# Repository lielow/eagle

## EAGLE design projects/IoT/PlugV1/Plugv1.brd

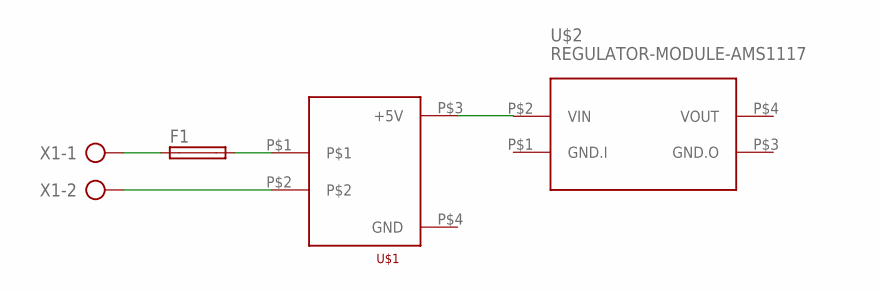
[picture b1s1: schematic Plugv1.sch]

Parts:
F1: SH22,5A
U$1: HLK-PM01
U$2: REGULATOR-MODULE-AMS1117
X1: AK500/2-H

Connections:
unnamed: F1.2, U$1.P$1
unnamed: F1.1, X1.1
unnamed: U$1.P$2, X1.2

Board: 2 copper layers, 4 parts (0 on the bottom side), 3 nets, no tracks yet.

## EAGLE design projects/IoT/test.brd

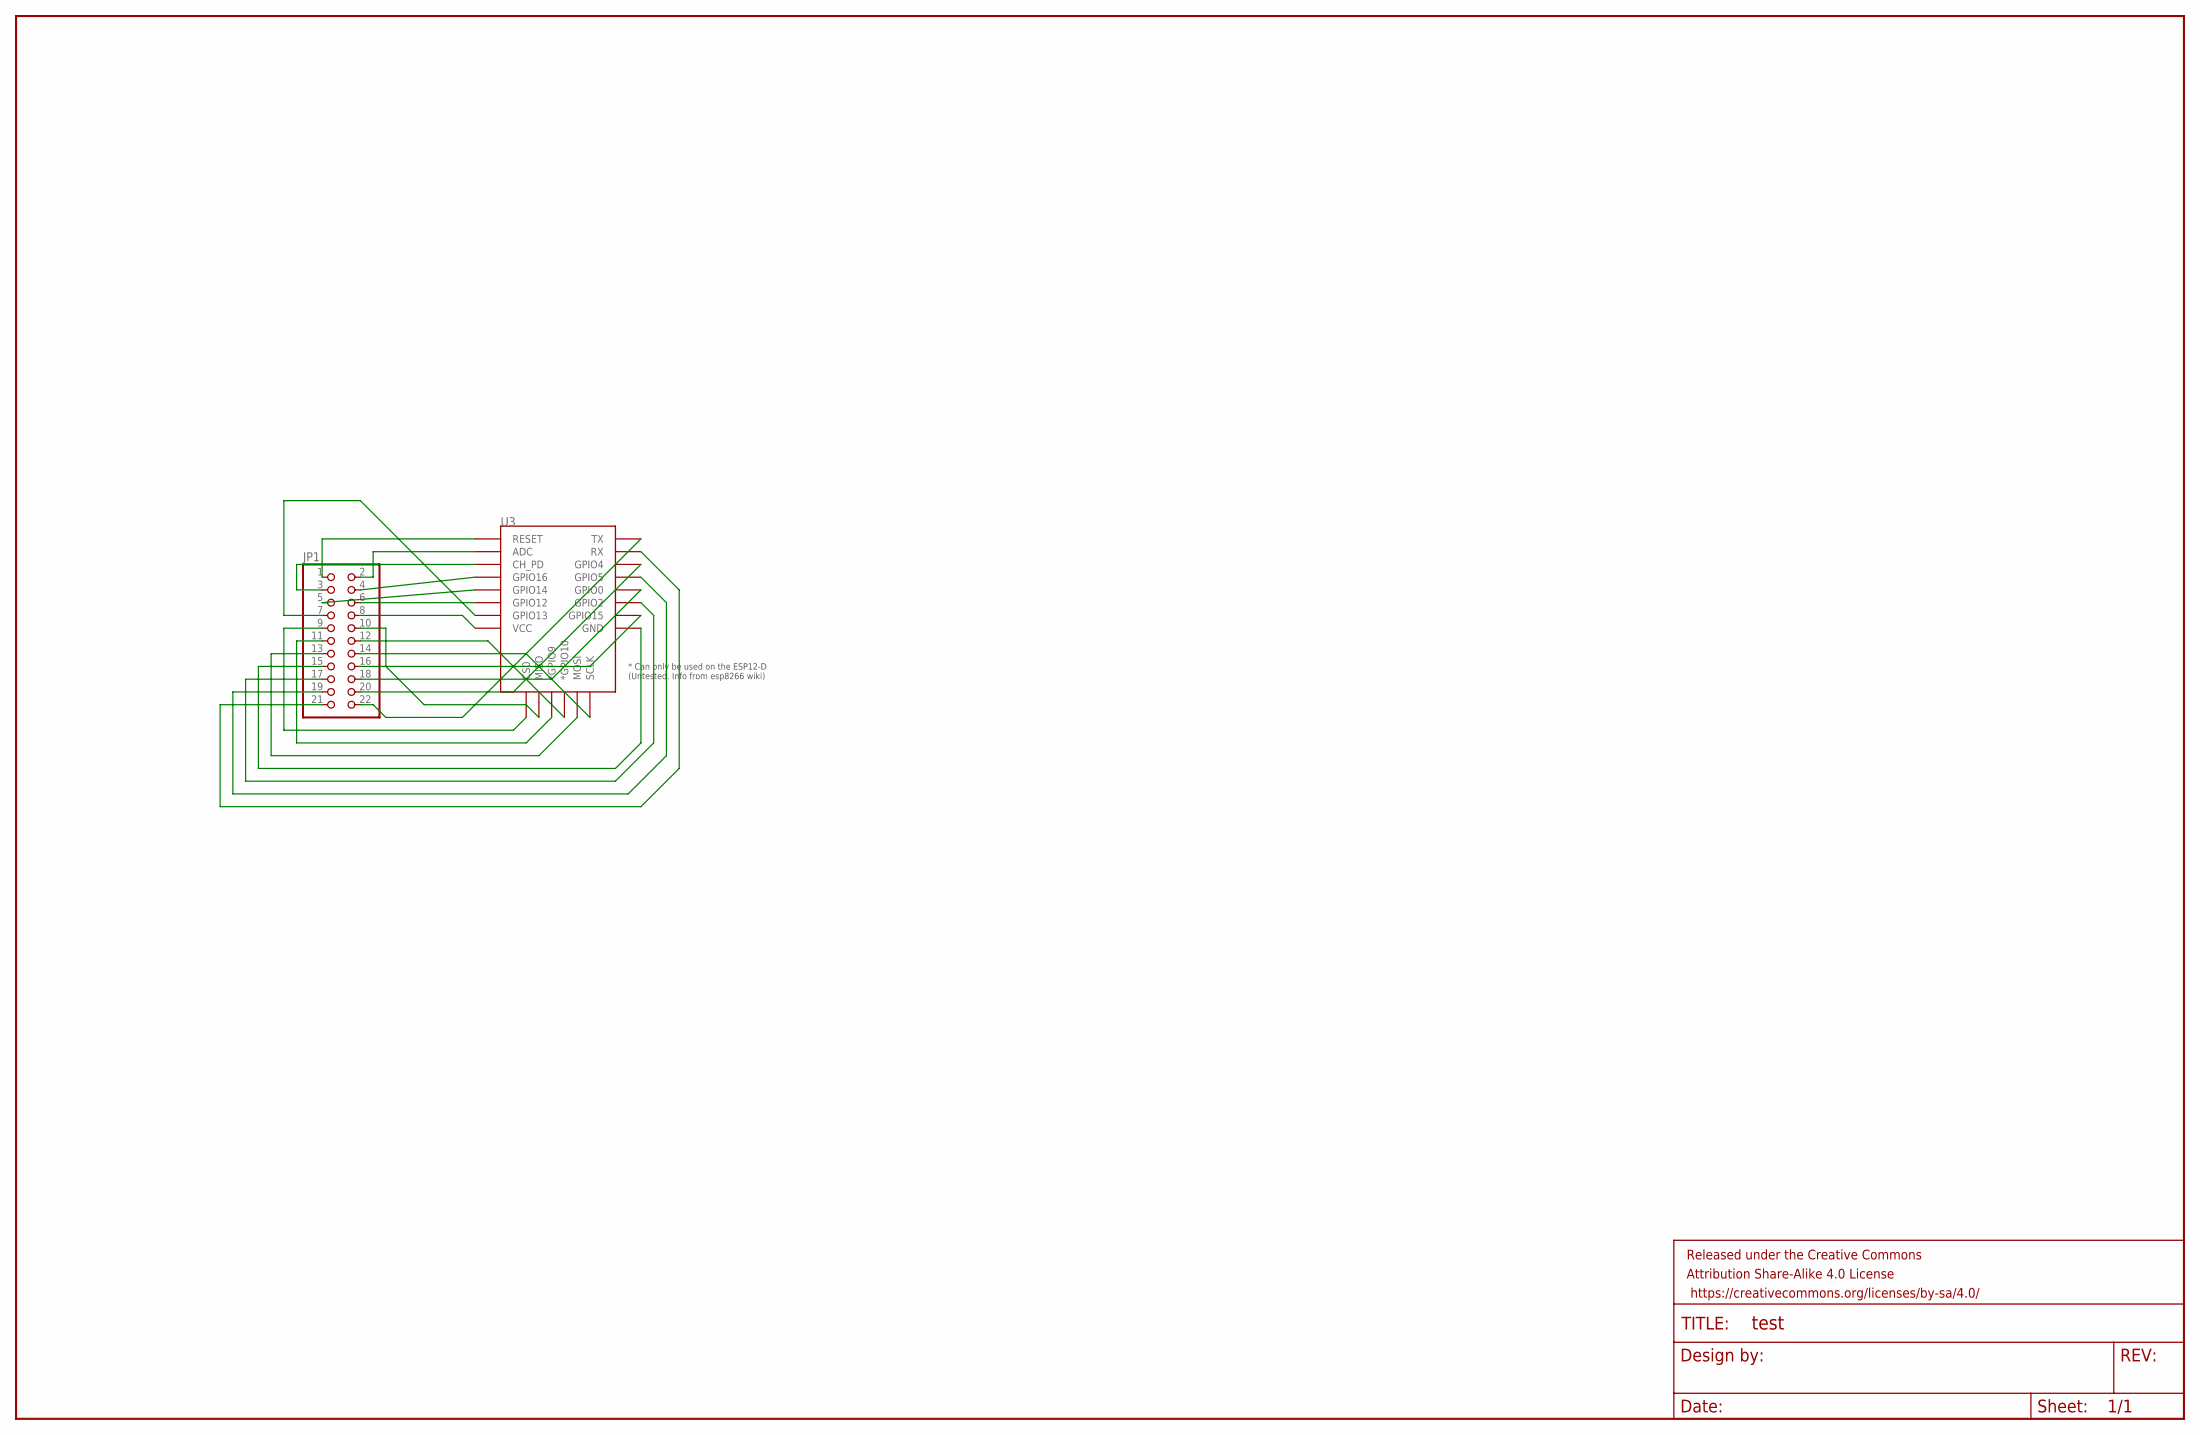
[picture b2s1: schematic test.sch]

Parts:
FRAME1: FRAME-LEDGER; CREATIVE_COMMONS
JP1: PINHD-2X11/90; 2X11/90
U3: ESP12ESMD; ESP12E-SMD

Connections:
unnamed: JP1.1, U3.RESET
unnamed: JP1.2, U3.ADC
unnamed: JP1.3, U3.CH_PD
unnamed: JP1.4, U3.GPIO16
unnamed: JP1.5, U3.GPIO14
unnamed: JP1.6, U3.GPIO12
unnamed: JP1.7, U3.GPIO13
unnamed: JP1.8, U3.VCC
unnamed: JP1.9, U3.CS0
unnamed: JP1.10, U3.MISO
unnamed: JP1.11, U3.GPIO9 (*GPIO9)
unnamed: JP1.12, U3.GPIO10 (*GPIO10)
unnamed: JP1.13, U3.MOSI
unnamed: JP1.14, U3.SCLK
unnamed: JP1.15, U3.GND
unnamed: JP1.16, U3.GPIO15
unnamed: JP1.17, U3.GPIO2
unnamed: JP1.18, U3.GPIO0
unnamed: JP1.19, U3.GPIO5
unnamed: JP1.20, U3.GPIO4
unnamed: JP1.21, U3.RXD0 (RX)
unnamed: JP1.22, U3.TXD0 (TX)

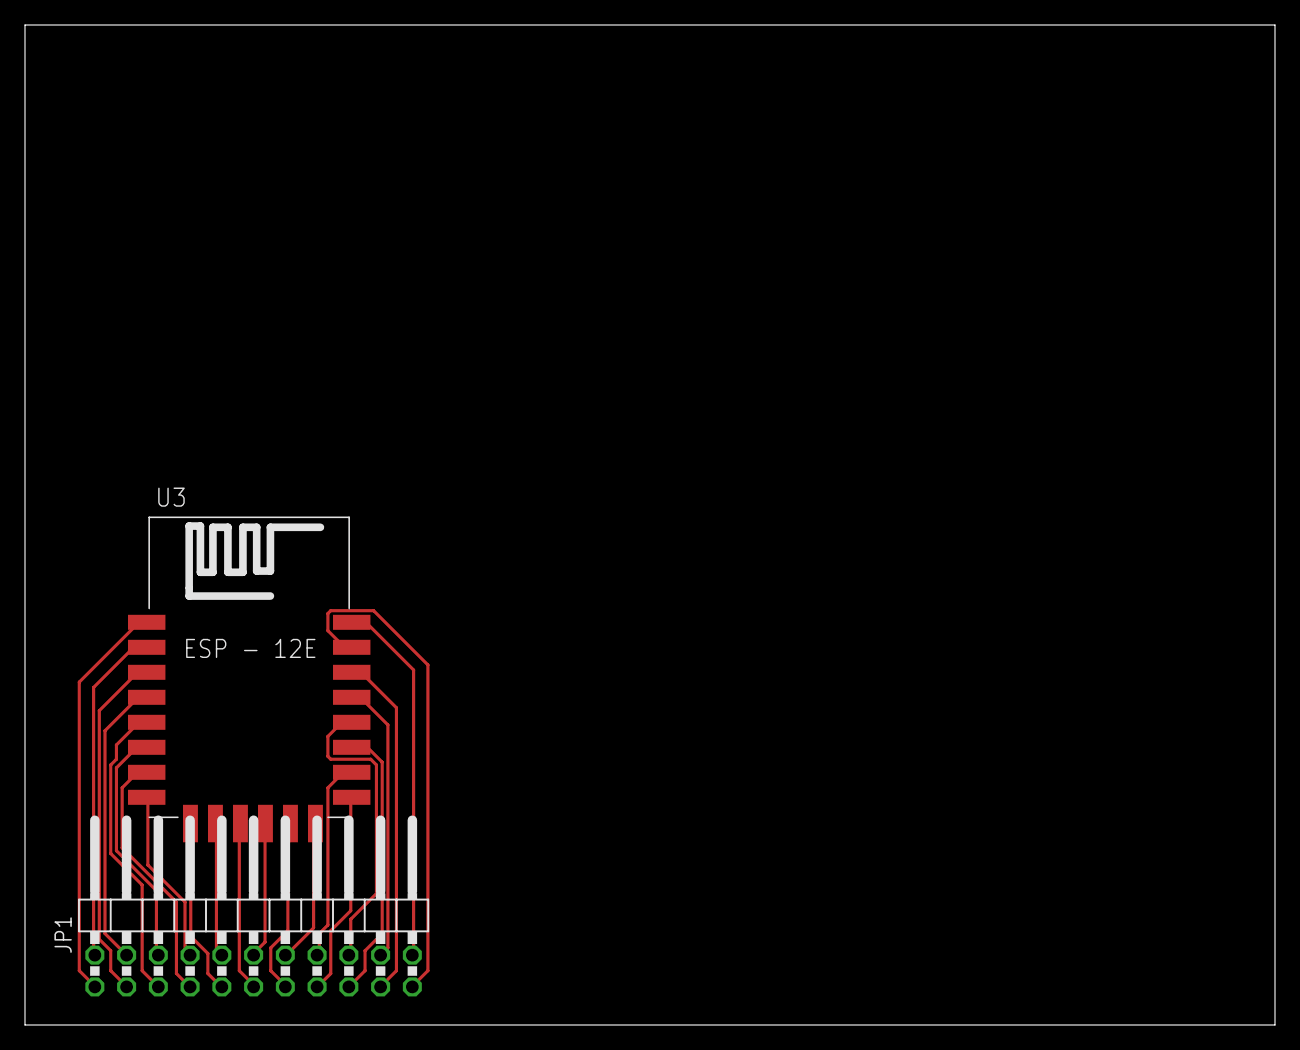
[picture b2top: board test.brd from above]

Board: 2 copper layers, 100.0 x 80.0 mm, 3 parts (0 on the bottom side), 22 nets.

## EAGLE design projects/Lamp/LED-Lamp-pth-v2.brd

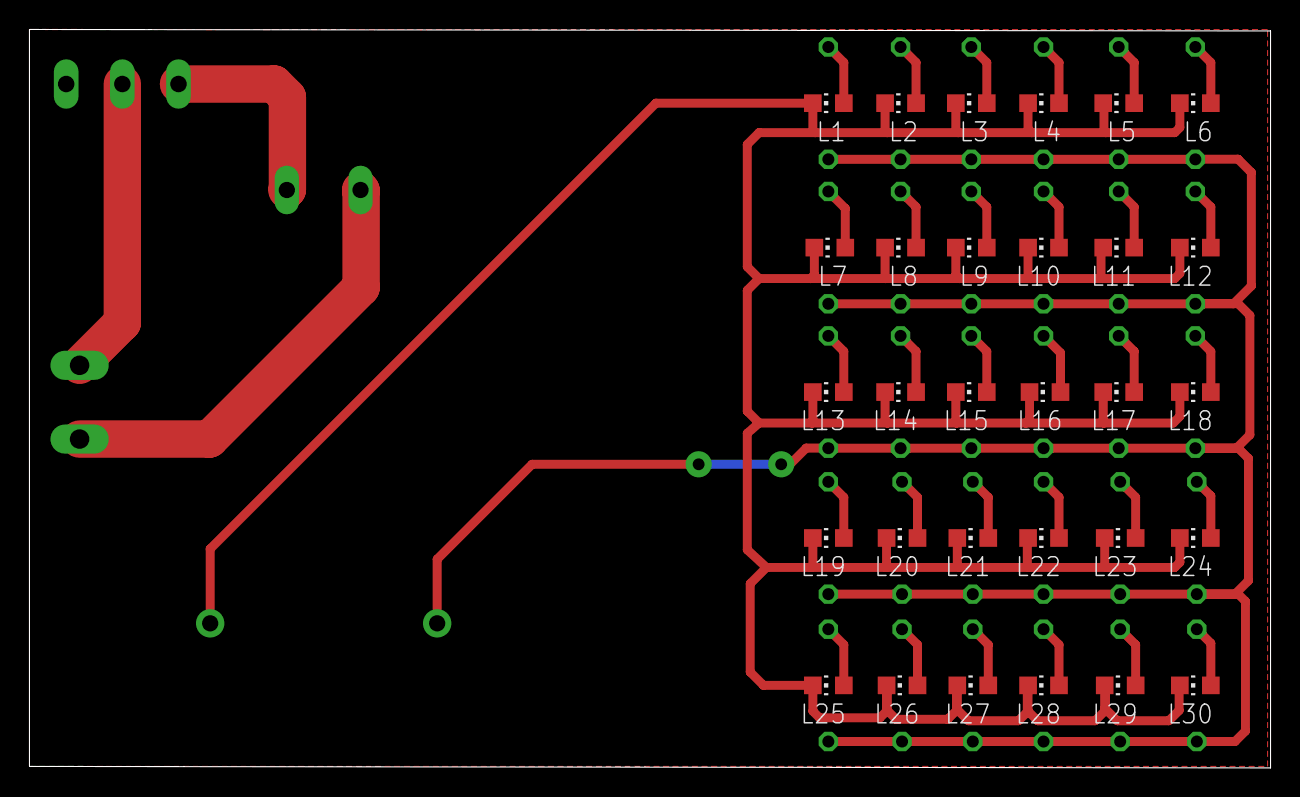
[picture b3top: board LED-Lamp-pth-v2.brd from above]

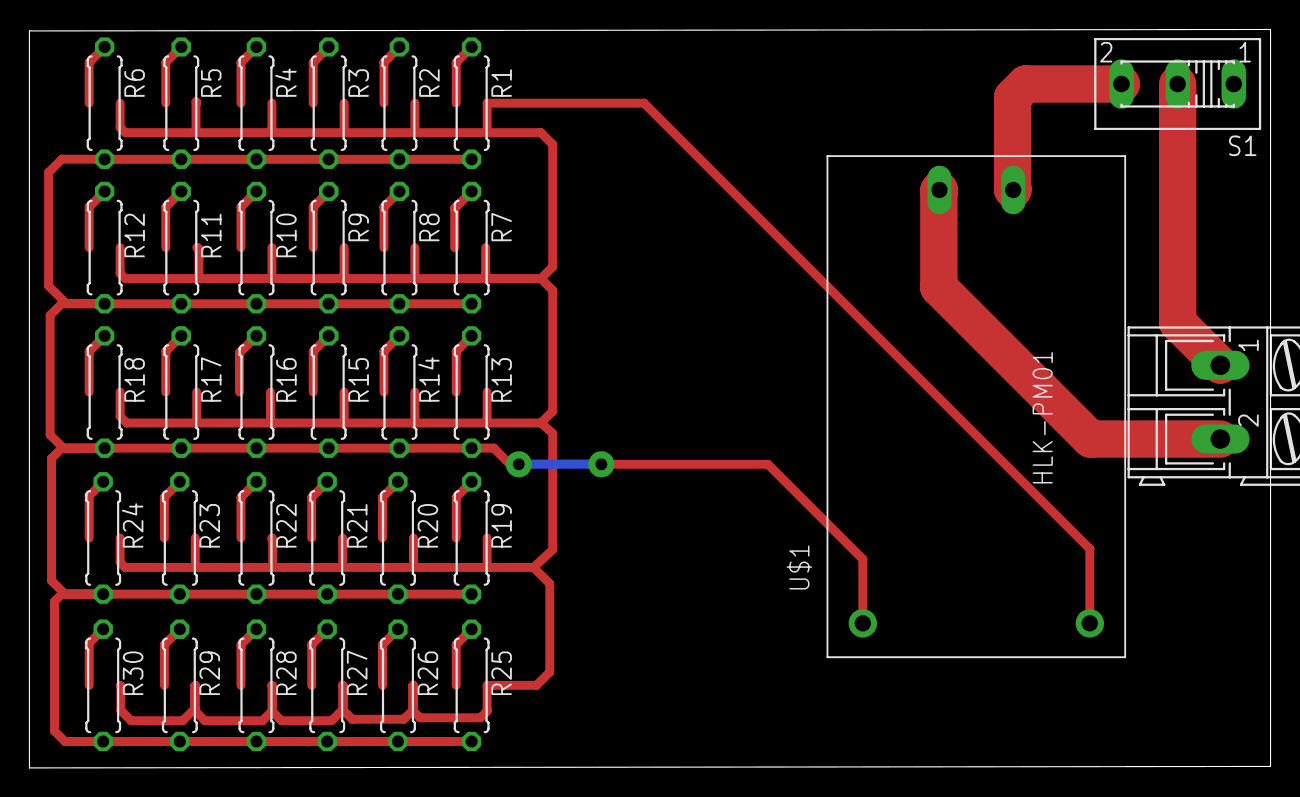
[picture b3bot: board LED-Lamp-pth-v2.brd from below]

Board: 2 copper layers, 84.2 x 50.1 mm, 63 parts (33 on the bottom side), 35 nets.

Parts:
L1, L2, L3, L4, L5, L6, L7, L8, L9, L10, L11, L12, L13, L14, L15, L16, L17, L18, L19, L20, L21, L22, L23, L24, L25, L26, L27, L28, L29, L30: CHIP-LED0805
R1, R2, R3, R4, R5, R6, R7, R8, R9, R10, R11, R12, R13, R14, R15, R16, R17, R18, R19, R20, R21, R22, R23, R24, R25, R26, R27, R28, R29, R30: 0207/7
S1: 255SB
U$1: HLK-PM01
X1: AK300/2

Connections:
GND: L1.C, L2.C, L3.C, L4.C, L5.C, L6.C, L7.C, L8.C, L9.C, L10.C, L11.C, L12.C, L13.C, L14.C, L15.C, L16.C, L17.C, L18.C, L19.C, L20.C, L21.C, L22.C, L23.C, L24.C, L25.C, L26.C, L27.C, L28.C, L29.C, L30.C, U$1.GND
unnamed: L2.A, R2.1
unnamed: L3.A, R3.1
unnamed: L4.A, R4.1
unnamed: L5.A, R5.1
unnamed: L6.A, R6.1
unnamed: L7.A, R7.1
unnamed: L8.A, R8.1
unnamed: L9.A, R9.1
unnamed: L10.A, R10.1
unnamed: L11.A, R11.1
unnamed: L12.A, R12.1
unnamed: L13.A, R13.1
unnamed: L14.A, R14.1
unnamed: L15.A, R15.1
unnamed: L16.A, R16.1
unnamed: L17.A, R17.1
unnamed: L18.A, R18.1
unnamed: L19.A, R19.1
unnamed: L20.A, R20.1
unnamed: L21.A, R21.1
unnamed: L22.A, R22.1
unnamed: L23.A, R23.1
unnamed: L24.A, R24.1
unnamed: L25.A, R25.1
unnamed: L26.A, R26.1
unnamed: L27.A, R27.1
unnamed: S1.2, X1.1
unnamed: L28.A, R28.1
unnamed: U$1.AC2, X1.2
unnamed: L29.A, R29.1
unnamed: L1.A, R1.1
unnamed: L30.A, R30.1
unnamed: R1.2, R2.2, R3.2, R4.2, R5.2, R6.2, R7.2, R8.2, R9.2, R10.2, R11.2, R12.2, R13.2, R14.2, R15.2, R16.2, R17.2, R18.2, R19.2, R20.2, R21.2, R22.2, R23.2, R24.2, R25.2, R26.2, R27.2, R28.2, R29.2, R30.2, U$1.+5V
unnamed: S1.3, U$1.AC1

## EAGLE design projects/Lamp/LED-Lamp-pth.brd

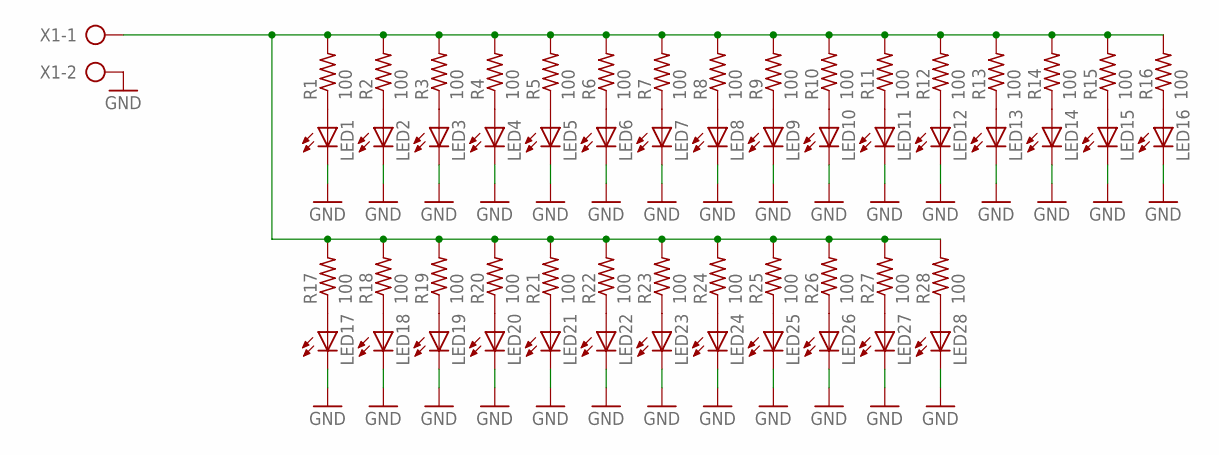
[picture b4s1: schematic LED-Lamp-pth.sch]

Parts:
LED1, LED2, LED3, LED4, LED5, LED6, LED7, LED8, LED9, LED10, LED11, LED12, LED13, LED14, LED15, LED16, LED17, LED18, LED19, LED20, LED21, LED22, LED23, LED24, LED25, LED26, LED27, LED28: LEDSML0805; SML0805
R1, R2, R3, R4, R5, R6, R7, R8, R9, R10, R11, R12, R13, R14, R15, R16, R17, R18, R19, R20, R21, R22, R23, R24, R25, R26, R27, R28: 100; 0207/7
X1: AK300/2

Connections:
GND: LED1.C, LED2.C, LED3.C, LED4.C, LED5.C, LED6.C, LED7.C, LED8.C, LED9.C, LED10.C, LED11.C, LED12.C, LED13.C, LED14.C, LED15.C, LED16.C, LED17.C, LED18.C, LED19.C, LED20.C, LED21.C, LED22.C, LED23.C, LED24.C, LED25.C, LED26.C, LED27.C, LED28.C, X1.2
unnamed: LED1.A, R1.1
unnamed: LED2.A, R2.1
unnamed: LED3.A, R3.1
unnamed: LED4.A, R4.1
unnamed: R1.2, R2.2, R3.2, R4.2, R5.2, R6.2, R7.2, R8.2, R9.2, R10.2, R11.2, R12.2, R13.2, R14.2, R15.2, R16.2, R17.2, R18.2, R19.2, R20.2, R21.2, R22.2, R23.2, R24.2, R25.2, R26.2, R27.2, R28.2, X1.1
unnamed: LED5.A, R5.1
unnamed: LED6.A, R6.1
unnamed: LED7.A, R7.1
unnamed: LED8.A, R8.1
unnamed: LED9.A, R9.1
unnamed: LED10.A, R10.1
unnamed: LED11.A, R11.1
unnamed: LED12.A, R12.1
unnamed: LED13.A, R13.1
unnamed: LED14.A, R14.1
unnamed: LED15.A, R15.1
unnamed: LED16.A, R16.1
unnamed: LED17.A, R17.1
unnamed: LED18.A, R18.1
unnamed: LED19.A, R19.1
unnamed: LED20.A, R20.1
unnamed: LED21.A, R21.1
unnamed: LED22.A, R22.1
unnamed: LED23.A, R23.1
unnamed: LED24.A, R24.1
unnamed: LED25.A, R25.1
unnamed: LED26.A, R26.1
unnamed: LED27.A, R27.1
unnamed: LED28.A, R28.1

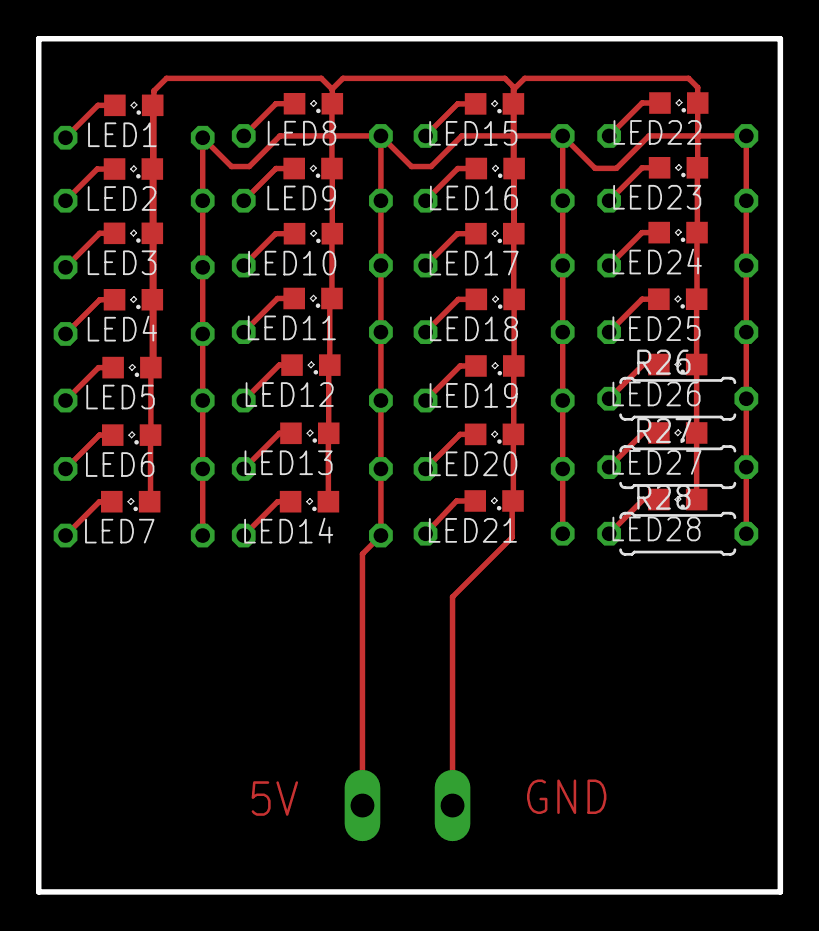
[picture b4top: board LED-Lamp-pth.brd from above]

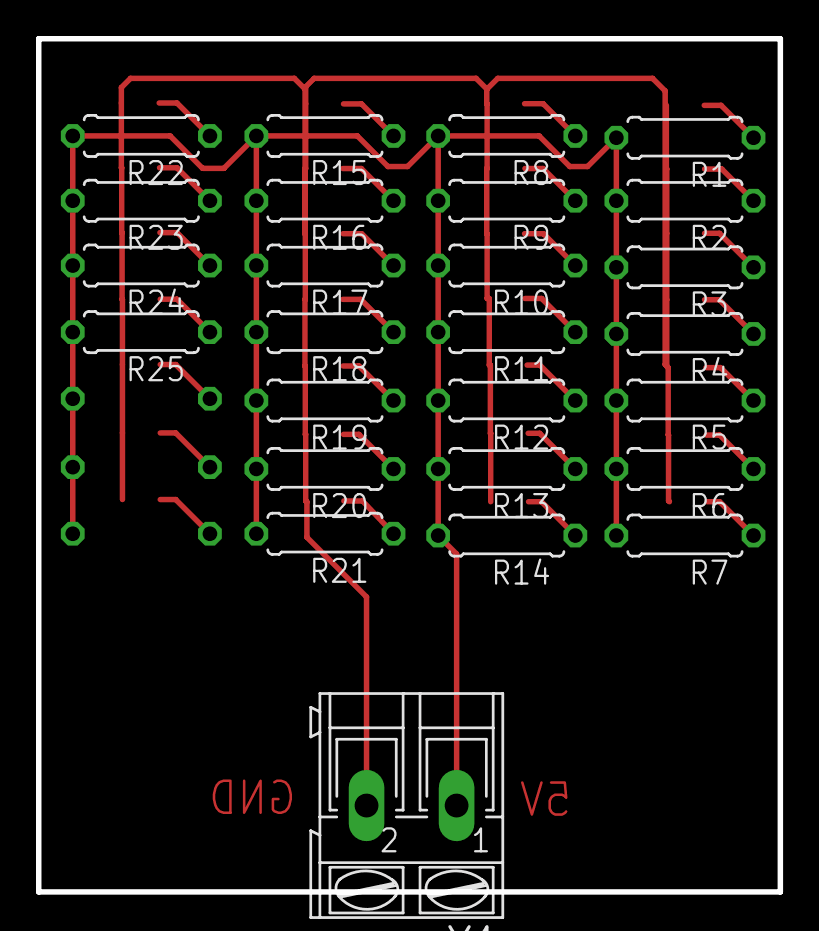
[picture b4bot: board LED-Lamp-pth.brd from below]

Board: 2 copper layers, 41.2 x 47.4 mm, 57 parts (26 on the bottom side), 30 nets.

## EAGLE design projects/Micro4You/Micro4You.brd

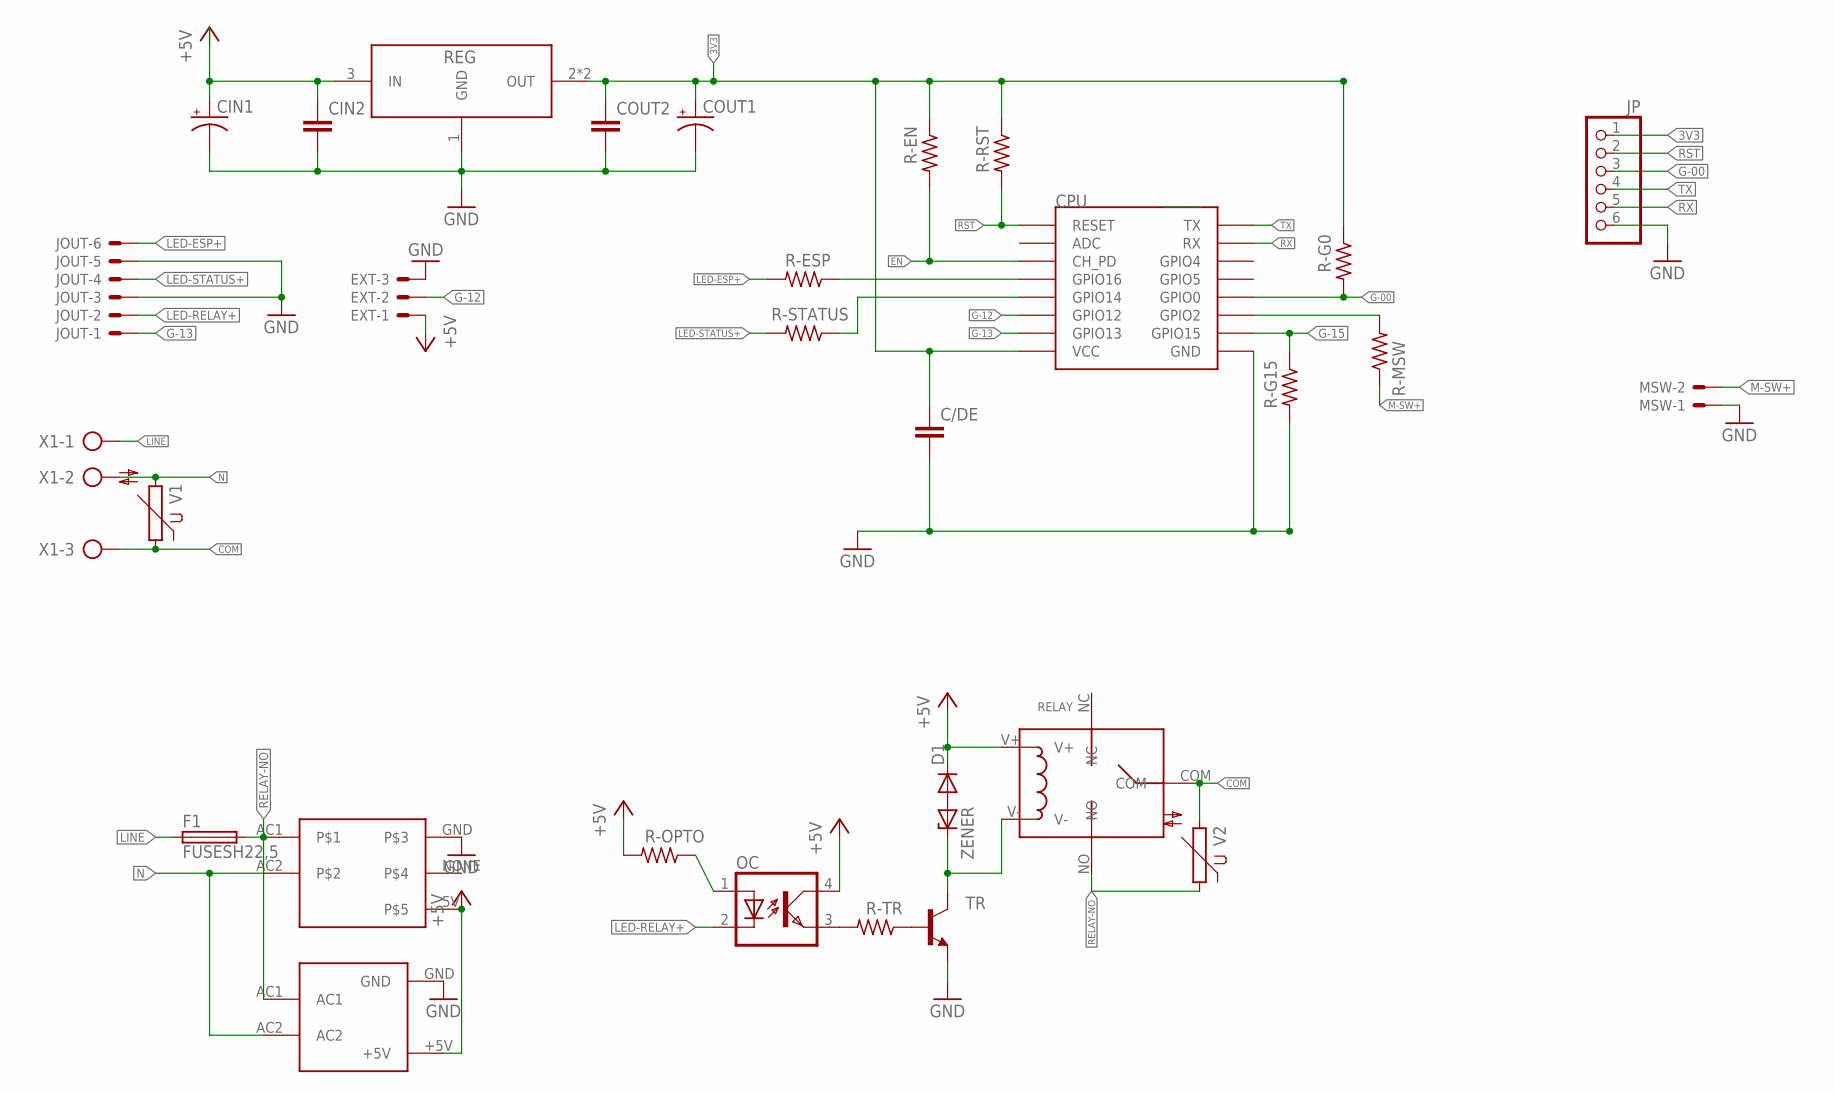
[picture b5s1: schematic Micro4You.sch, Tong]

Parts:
C/DE: C-EUC0805; C0805
CIN1: CPOL-USE2.5-5; E2,5-5
CIN2: C-EUC0805; C0805
COUT1: CPOL-USE2.5-5; E2,5-5
COUT2: C-EUC0805; C0805
CPU: ESP12SMD; ESP12-SMD
D1: 1N4148DO35-7; DO35-7
EXT: 53048-03
F1: FUSESH22,5; SH22,5
HLK: HLK-PM01
JOUT: 53048-06
JP: PINHD-1X6; 1X06
MSW: 53048-02
OC: PC817; DIL04
R-EN: R-US_M0805; M0805
R-ESP: R-US_M0805; M0805
R-G0, R-G15: R-US_M0805; M0805
R-MSW: R-US_M0805; M0805
R-OPTO: R-US_M0805; M0805
R-RST: R-US_M0805; M0805
R-STATUS: R-US_M0805; M0805
R-TR: R-US_M0805; M0805
REG: AMS1117-3.3; SOT-223
RELAY: RELAY-SONGLE
TR: BC817-16SMD; SOT23-BEC
U$4: POWERSUPPLY-5V-700MA
V1, V2: S14K11
X1: AK300/3
ZENER: 1N4728; DO41Z10

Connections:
3V3: C/DE.1, COUT1.+, COUT2.1, CPU.VCC, JP.1, R-EN.1, R-G0.1, R-RST.1, REG.2 (OUT), REG.4 (OUT)
+5V: CIN1.+, CIN2.1, D1.C, EXT.1, HLK.+5V, OC.4 (COL), R-OPTO.2, REG.3 (IN), RELAY.V+, U$4.5V
COM: RELAY.COM, V1.1, V2.2, X1.3
EN: CPU.CH_PD, R-EN.2
G-00: CPU.GPIO0, JP.3, R-G0.2
G-12: CPU.GPIO12, EXT.2
G-13: CPU.GPIO13, JOUT.1
G-15: CPU.GPIO15, R-G15.1
GND: C/DE.2, CIN1.-, CIN2.2, COUT1.-, COUT2.2, CPU.GND, EXT.3, HLK.GND, JOUT.3, JOUT.5, JP.6, MSW.1, R-G15.2, REG.1 (GND), TR.E, U$4.GND
LED-ESP+: JOUT.6, R-ESP.2
LED-RELAY+: JOUT.2, OC.2 (C)
LED-STATUS+: JOUT.4, R-STATUS.2
LINE: F1.1, X1.1
M-SW+: MSW.2, R-MSW.1
N: HLK.AC2, U$4.AC2, V1.2, X1.2
unnamed: OC.3 (EMIT), R-TR.2
unnamed: R-TR.1, TR.B
unnamed: CPU.GPIO2, R-MSW.2
unnamed: CPU.GPIO14, R-STATUS.1
unnamed: OC.1 (A), R-OPTO.1
unnamed: D1.A, ZENER.A
unnamed: RELAY.V-, TR.C, ZENER.C
unnamed: CPU.GPIO16, R-ESP.1
RELAY-NO: F1.2, HLK.AC1, RELAY.NO, U$4.AC1, V2.1
RST: CPU.RESET, JP.2, R-RST.2
RX: CPU.RXD0 (RX), JP.5
TX: CPU.TXD0 (TX), JP.4

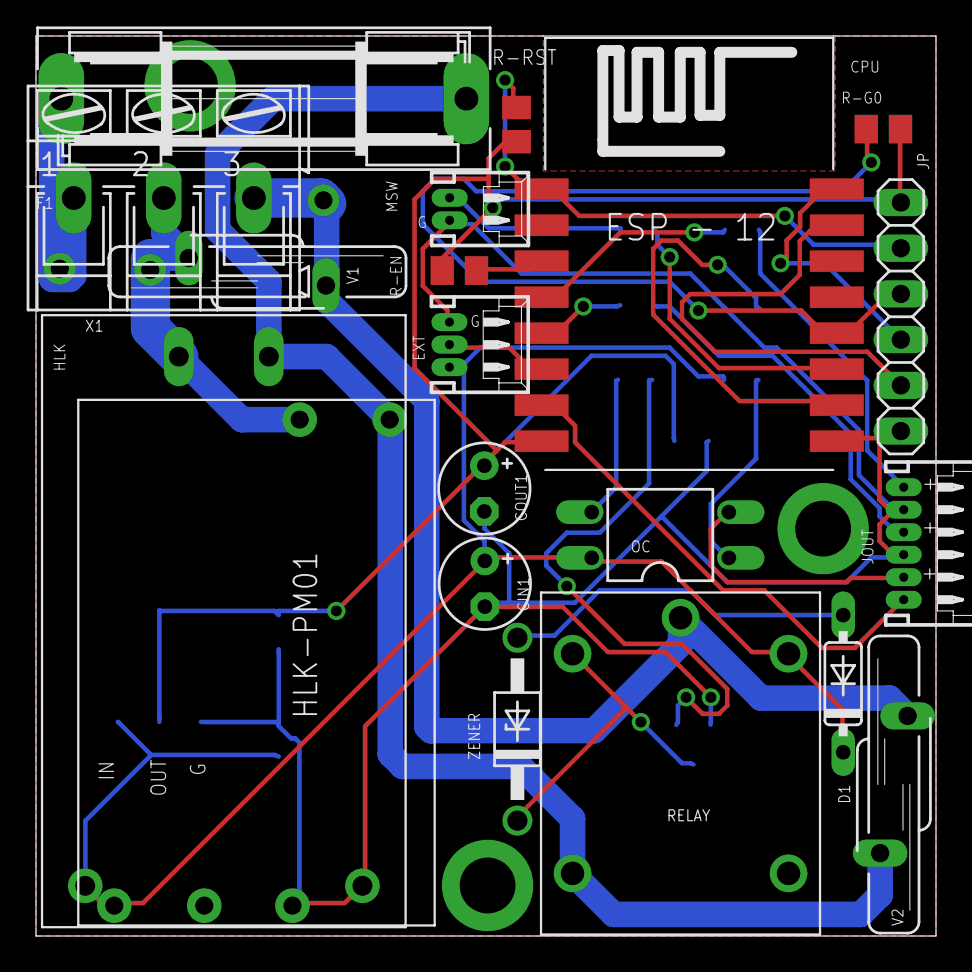
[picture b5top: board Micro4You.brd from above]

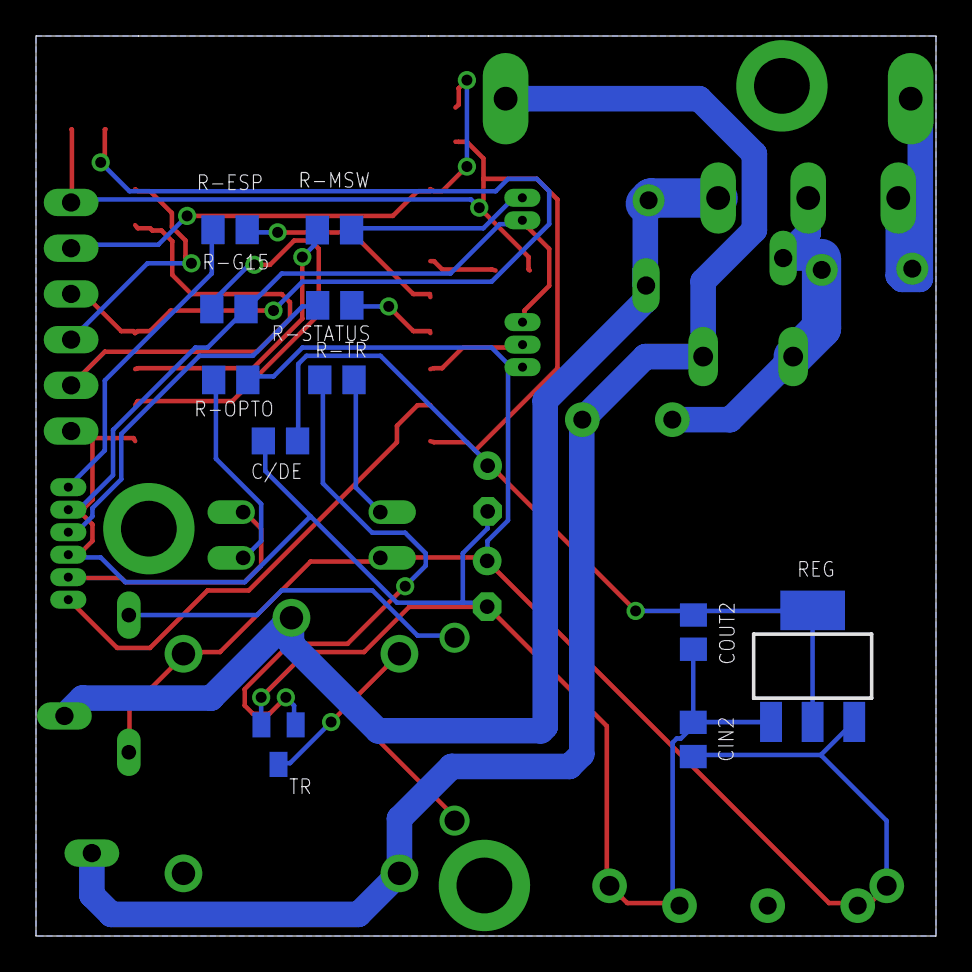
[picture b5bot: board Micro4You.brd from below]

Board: 2 copper layers, 50.0 x 50.0 mm, 31 parts (11 on the bottom side), 27 nets.

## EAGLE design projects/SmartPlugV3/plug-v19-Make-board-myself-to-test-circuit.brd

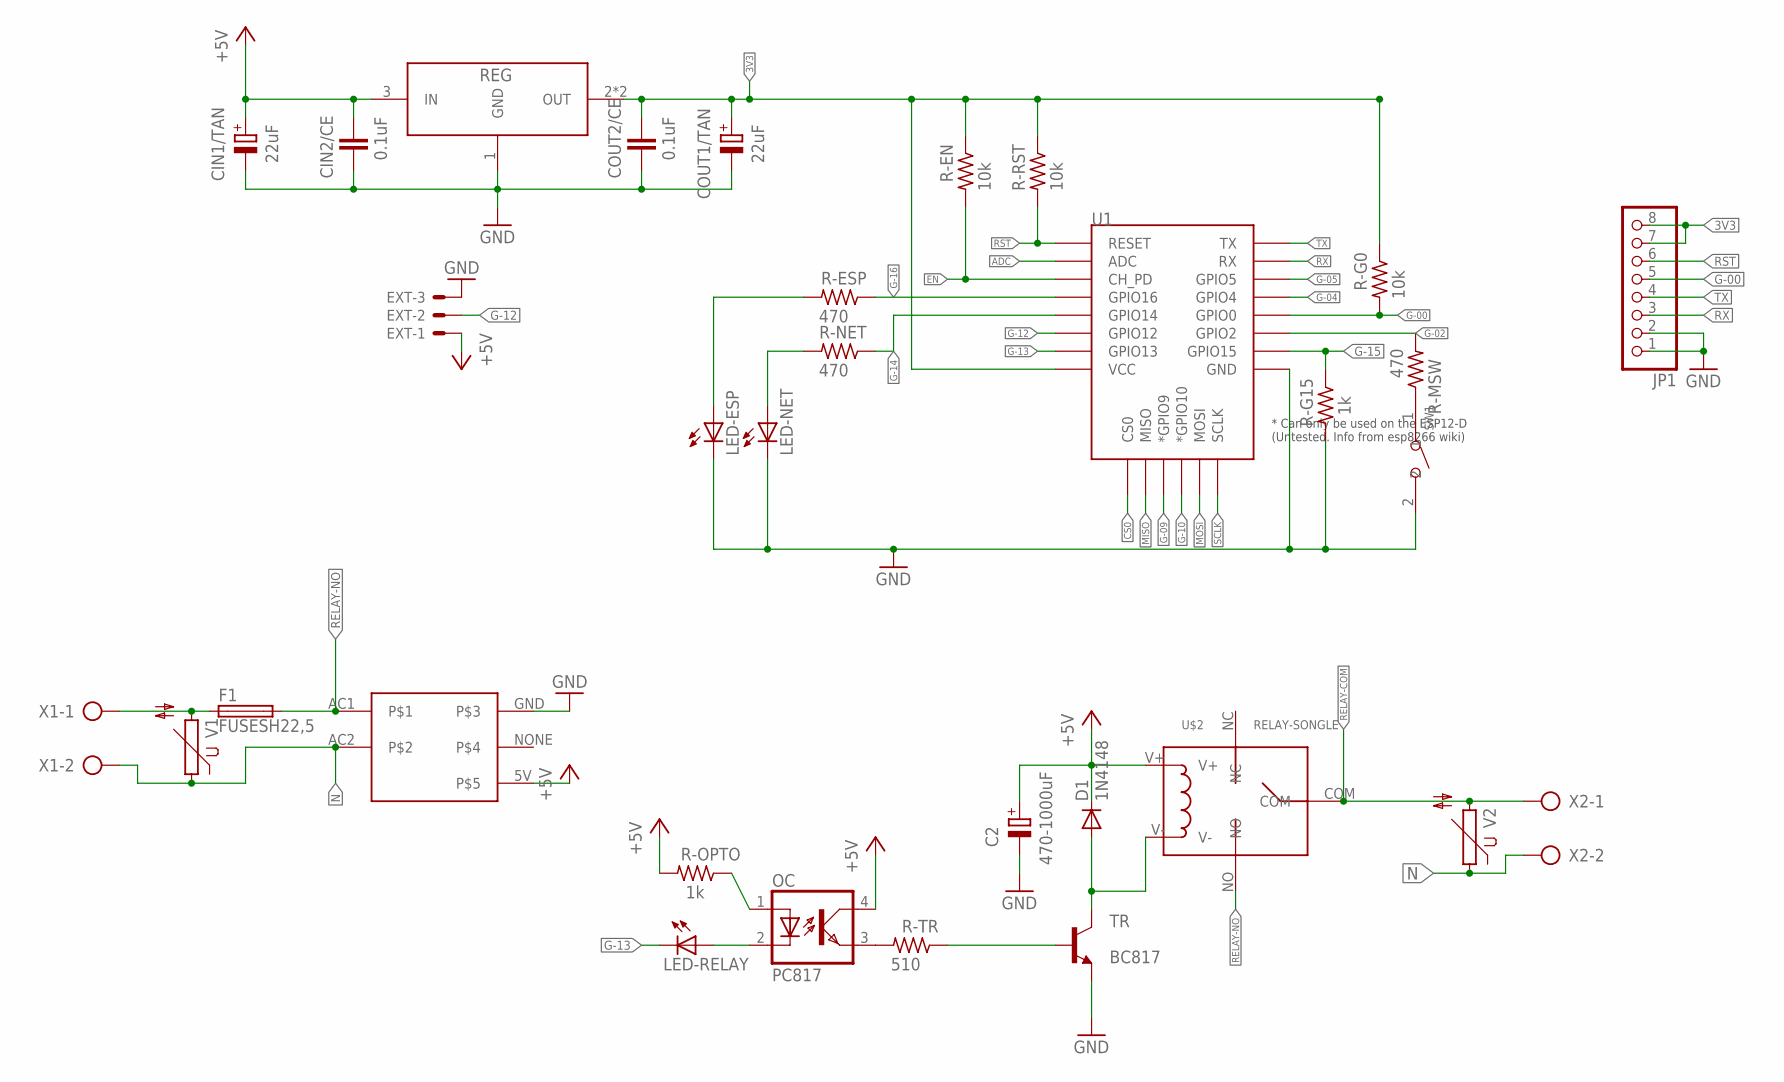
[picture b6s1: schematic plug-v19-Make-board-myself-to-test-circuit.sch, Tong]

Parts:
C2: 470-1000uF; E3,5-8
CIN1/TAN: 22uF; B/3528-21R
CIN2/CE: 0.1uF; C0805K
COUT1/TAN: 22uF; B/3528-21R
COUT2/CE: 0.1uF; C0805K
D1: 1N4148; DO35-7
EXT: 53048-03
F1: FUSESH22,5; SH22,5
JP1: PINHD-1X8; 1X08
LED-ESP: LEDCHIPLED_0805; CHIPLED_0805
LED-NET: LEDCHIPLED_0805; CHIPLED_0805
LED-RELAY: LEDCHIPLED_0805; CHIPLED_0805
OC: PC817; DIL04
R-EN: 10k; M0805
R-ESP: 470; M0805
R-G0: 10k; M0805
R-G15: 1k; M0805
R-MSW: 470; M0805
R-NET: 470; M0805
R-OPTO: 1k; M0805
R-RST: 10k; M0805
R-TR: 510; M0805
REG: AMS1117-3.3; SOT-223
SW1: DIP-BUTTON(2P-6.0X3.0X4.3MM)-TS-1101F; SW2-5.0-6.0X3.0X4.3MM
TR: BC817; SOT23-BEC
U1: ESP12ESMD; ESP12E-SMD
U$2: RELAY-SONGLE
U$4: POWERSUPPLY-5V-700MA
V1, V2: S14K11
X1, X2: AK300/2

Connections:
3V3: COUT1/TAN.+, COUT2/CE.1, JP1.7, JP1.8, R-EN.1, R-G0.1, R-RST.1, REG.2 (OUT), REG.4 (OUT), U1.VCC
+5V: C2.+, CIN1/TAN.+, CIN2/CE.1, D1.C, EXT.1, OC.4 (COL), R-OPTO.2, REG.3 (IN), U$2.V+, U$4.5V
ADC: U1.ADC
CS0: U1.CS0
EN: R-EN.2, U1.CH_PD
G-00: JP1.5, R-G0.2, U1.GPIO0
G-02: R-MSW.2, U1.GPIO2
G-04: U1.GPIO4
G-05: U1.GPIO5
G-09: U1.GPIO9 (*GPIO9)
G-10: U1.GPIO10 (*GPIO10)
G-12: EXT.2, U1.GPIO12
G-13: LED-RELAY.C, U1.GPIO13
G-14: R-NET.1, U1.GPIO14
G-15: R-G15.1, U1.GPIO15
G-16: R-ESP.1, U1.GPIO16
GND: C2.-, CIN1/TAN.-, CIN2/CE.2, COUT1/TAN.-, COUT2/CE.2, EXT.3, JP1.1, JP1.2, LED-ESP.C, LED-NET.C, R-G15.2, REG.1 (GND), SW1.2, TR.E, U1.GND, U$4.GND
LINE: F1.1, V1.2, X1.1
MISO: U1.MISO
MOSI: U1.MOSI
N: U$4.AC2, V1.1, V2.1, X1.2, X2.2
unnamed: OC.3 (EMIT), R-TR.2
unnamed: R-TR.1, TR.B
unnamed: LED-ESP.A, R-ESP.2
unnamed: OC.1 (A), R-OPTO.1
unnamed: LED-NET.A, R-NET.2
unnamed: D1.A, TR.C, U$2.V-
unnamed: LED-RELAY.A, OC.2 (C)
unnamed: R-MSW.1, SW1.1
RELAY-COM: U$2.COM, V2.2, X2.1
RELAY-NO: F1.2, U$2.NO, U$4.AC1
RST: JP1.6, R-RST.2, U1.RESET
RX: JP1.3, U1.RXD0 (RX)
SCLK: U1.SCLK
TX: JP1.4, U1.TXD0 (TX)

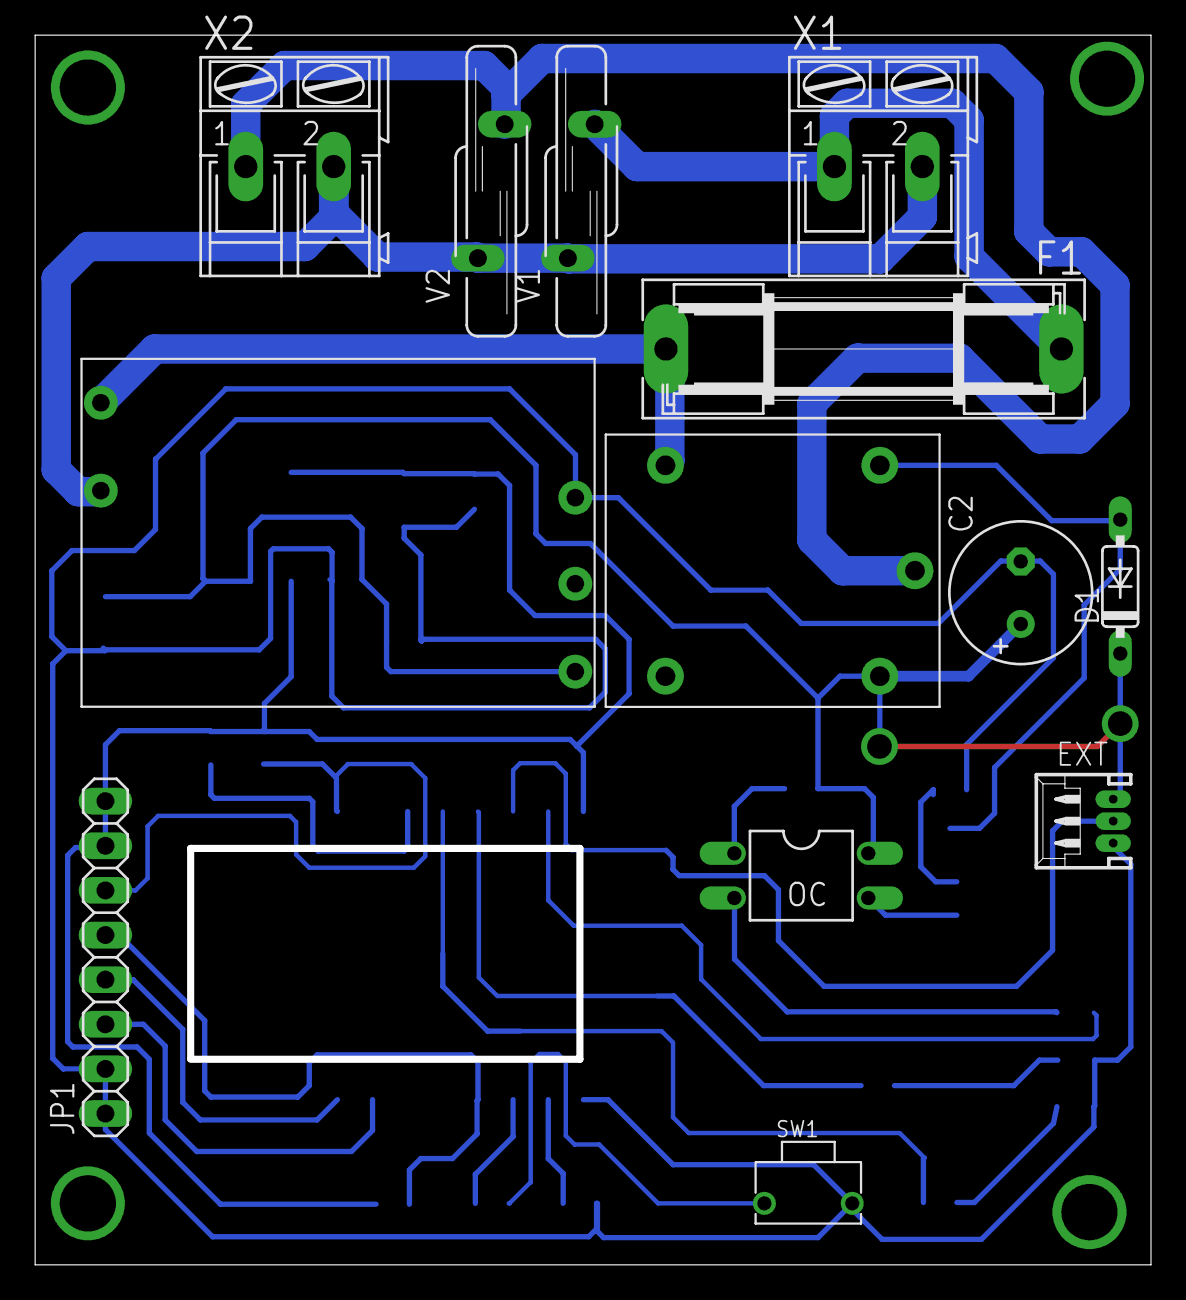
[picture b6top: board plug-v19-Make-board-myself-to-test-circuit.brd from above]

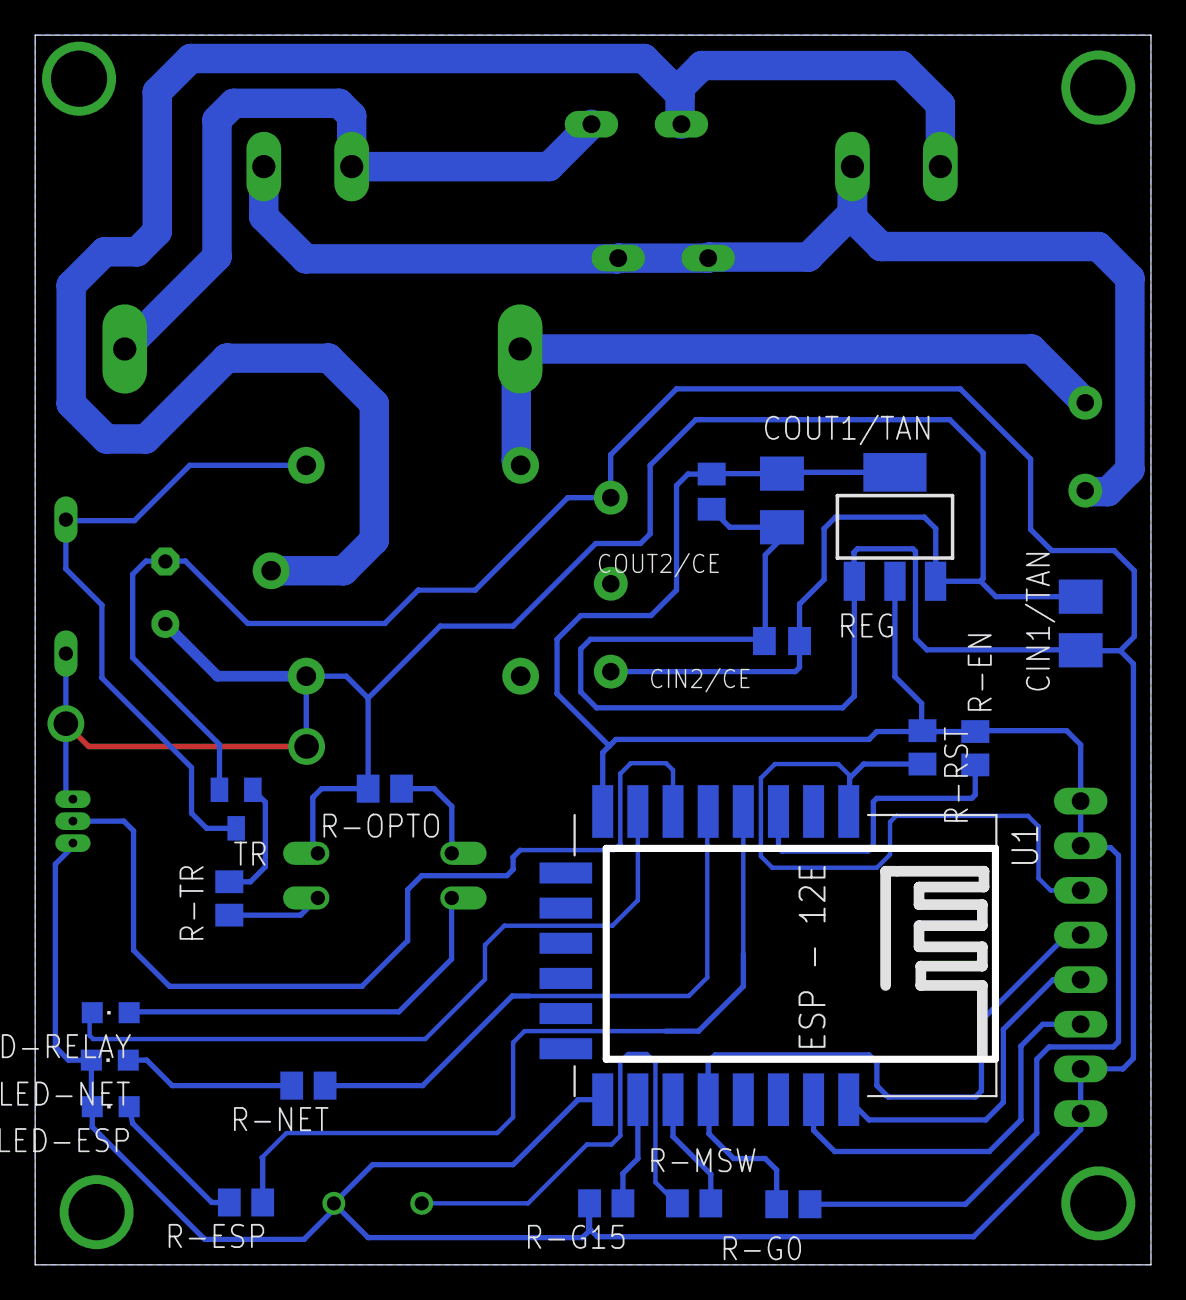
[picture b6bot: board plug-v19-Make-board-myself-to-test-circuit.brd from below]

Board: 2 copper layers, 63.5 x 70.0 mm, 32 parts (19 on the bottom side), 26 nets.

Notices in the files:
parts and their libraries:
SparkFun-Aesthetics: Licensing: Creative Commons ShareAlike 4.0 International - https://creativecommons.org/licenses/by-sa/4.0
SparkFun-Aesthetics: Released under the Creative Commons Attribution Share-Alike 4.0 License
SparkFun-Aesthetics: https://creativecommons.org/licenses/by-sa/4.0
